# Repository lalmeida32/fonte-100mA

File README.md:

# Projeto: Fonte-100mA — TRABALHO 01

### Grupo 19, Integrantes:

* Adrio O. Alves (*11796830*)
* Eduardo V. B. Rossi (*10716887*)
* Felipi Y. Santos (*11917292*)
* Lucas F. de Almeida (*1162063*)

**Docente**: Eduardo do Valle Simões
**Curso**: SSC0180 - Eletrônica para Computação

**Bacharelado em Ciências da Computação — 2020**
**Instituto de Ciências Matemáticas e de Computação**
**Universidade de São Paulo**

---

# Introdução

​	O projeto de trabalho 1 tem como objetivo a construção de uma fonte de alimentação genérica que precisa  fornecer corrente de até 100mA (*miliampères*) e uma tensão entre 3V e 12V. O projeto conta com um diagrama contendo os componentes eletrônicos escolhidos para construção da fonte, juntamente com o preço de cada um. Além disso, o projeto da fonte foi modelado em duas ferramentas de construção de circuitos: Falstad e EAGLE, e também um vídeo apresentando uma visão geral.

 # O repositório

* **estudo-do-projeto**

  * *Estudos.md*: Esse markdown dá informações do que cada componente eletrônico usado na fonte é, como ele é usado na fonte, isto é, seu papel.

  * **imagens**: fotos de peças/dependência do Estudos.md

  * *Dimensionamento.md*: relação de gastos e links para cada componente

* **arquivos-circuitos**

  * **FONTE**: arquivos do projeto no Eagle (contém esquemático e PCB)
  * *circuit-20200628-2337.circuitjs.txt*: um export do circuito feito no Falstad.
  * **EAGLE:** diretório contendo os arquivos do projeto no EAGLE
  * *eagle.jpg*: um export do projeto esquemático no EAGLE
  * *pcb.png*: um export do projeto em PCB no EAGLE
  * *circuito.png*: foto do circuito no falstad

# Diagrama da Fonte

# Relação componente/valores

**Obs**.: Desconsideramos o frete pois os preços de entrega encontram-se mais elevados durante o período da Pandemia (COVID-19). 

| Componente                                         | Links                                                        | Quantidade | Preço resultante           |
| -------------------------------------------------- | ------------------------------------------------------------ | ---------- | -------------------------- |
| **Transformador**               10+10 bivolt 800mA | https://produto.mercadolivre.com.br/MLB-1304934993-transformador-trafo-1010v-800ma-bivolt-eletrnica-_JM?matt_tool=82322591&matt_word&gclid=CjwKCAjwxLH3BRApEiwAqX9are-Hoqy3DhheSooU8NO5g_m_VOuyIxmSU64KT07Ga4GBR1CclxpqFRoCT10QAvD_BwE&quantity=1 | x1         | R$ 30,00                   |
| **Diodos da ponte retificadora** (1n4007)          | https://www.robocore.net/loja/itens-eletronicos/diodo-1n4007?gclid=CjwKCAjwxLH3BRApEiwAqX9arQYP_1w9nsWFqdvp4X-WlUcxEd8-nIBf6EI5o0YcvvptZfaJRTloMRoCyW0QAvD_BwE | x4         | R$ 0,18        x 4 =  0,72 |
| **Capacitor** eletrolítico 270uF / 50V             | https://produto.mercadolivre.com.br/MLB-1539705638-cap-eletrolitico-270uf-50v-kit-c-50-pcs-_JM?matt_tool=79246729&matt_word&gclid=Cj0KCQjw3Nv3BRC8ARIsAPh8hgJOoLrQkDYLJqg39wcG0bboEYxBCcrLzJXZ2tlZwHFAX_THqohX_jQaArT6EALw_wcB&quantity=1 | x1         | R$ 15,50                   |
| **Diodo Zener** (BZX55C 13V/0,5W)                  | https://www.baudaeletronica.com.br/diodo-zener-bzx55c-13v-0-5w.html | x1         | R$ 0,09                    |
| **Transistor NPN** (BC337)                         | https://www.robocore.net/loja/itens-eletronicos/transistor-npn-bc337?gclid=CjwKCAjwxLH3BRApEiwAqX9arW03jdNyoyxCW0BkSUH1jNxcEZlj1NO8uKe5adsfmaa_ggKm3B1-3hoC9gwQAvD_BwE | x1         | R$ 1,20                    |
| **Resistor** (1kΩ)                                 | https://www.robocore.net/loja/itens-eletronicos/resistor-1k-pacote-com-10-unidades?gclid=Cj0KCQjw3Nv3BRC8ARIsAPh8hgIWM1y2G34SD7-tczS923PPDzohgqbYDrJMymhz6VmJgYpguPpxyvwaAvVsEALw_wcB | x1         | R$ 0,75                    |
| **Resistor** (2.2kΩ)                               | https://www.eletroinfocia.com.br/resistor-1-4w-2k2?parceiro=5383&gclid=Cj0KCQjw3Nv3BRC8ARIsAPh8hgIYW0y8DoWLAFSC3mD8_5y1W9r2wVgBxpERvJd_8GI4131PIfijfdAaArM8EALw_wcB | x1         | R$ 0,10                    |
| **Potenciômetro**                                  | https://www.engetronic-sc.com.br/produtos/ver/321/potenciometro-linear-5k-l15---eixo-estriado-tracking-google-shopping?gclid=Cj0KCQjw3Nv3BRC8ARIsAPh8hgJ0FChjyK9vocYBgfldQy7j2Pse0-l_idTZ0iNpJngsEBgyiqvtofkaAqLBEALw_wcB | x1         | R$ 1,35                    |
| **TOTAL:**                                         |                                                              | 11         | R$ 49,72                   |

# Sobre os componentes não encontrados no EAGLE

​	Como o EAGLE não possui todos os componentes que foram utilizados na fonte, tivemos de utilizar componentes com funcionalidade e dimensões iguais no lugar.

# Links

* Vídeo explicativo da fonte: https://youtu.be/iQQ3Y2TPxfM
* Falstad (cópia em arquivos-circuitos): https://tinyurl.com/y8z7htxh
* Eagle (esquemático): https://imgur.com/a/H5OCaSa
* Eagle (PCB): https://imgur.com/a/zWWUykP

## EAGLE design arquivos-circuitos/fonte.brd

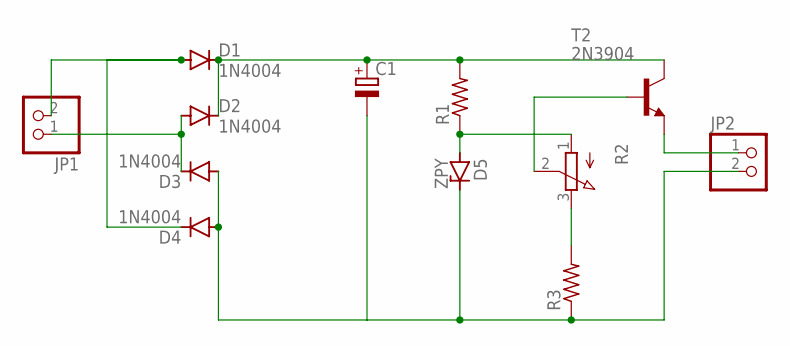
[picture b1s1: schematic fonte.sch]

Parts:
C1: CPOL-EUE3.5-10; E3,5-10
D1, D2, D3, D4: 1N4004; DO41-10
D5: ZPY; DO41Z10
JP1, JP2: PINHD-1X2; 1X02
R1, R3: R-US_0207/10; 0207/10
R2: 3RP/1610N
T2: 2N3904; TO92

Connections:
unnamed: D1.A, D4.C, JP1.2
unnamed: D2.A, D3.C, JP1.1
unnamed: JP2.1, T2.3 (E)
unnamed: C1.+, D1.C, D2.C, R1.2, T2.1 (C)
unnamed: D5.A, R1.1, R2.1 (A)
unnamed: R2.2 (S), T2.2 (B)
unnamed: R2.3 (E), R3.2
unnamed: C1.-, D3.A, D4.A, D5.C, JP2.2, R3.1

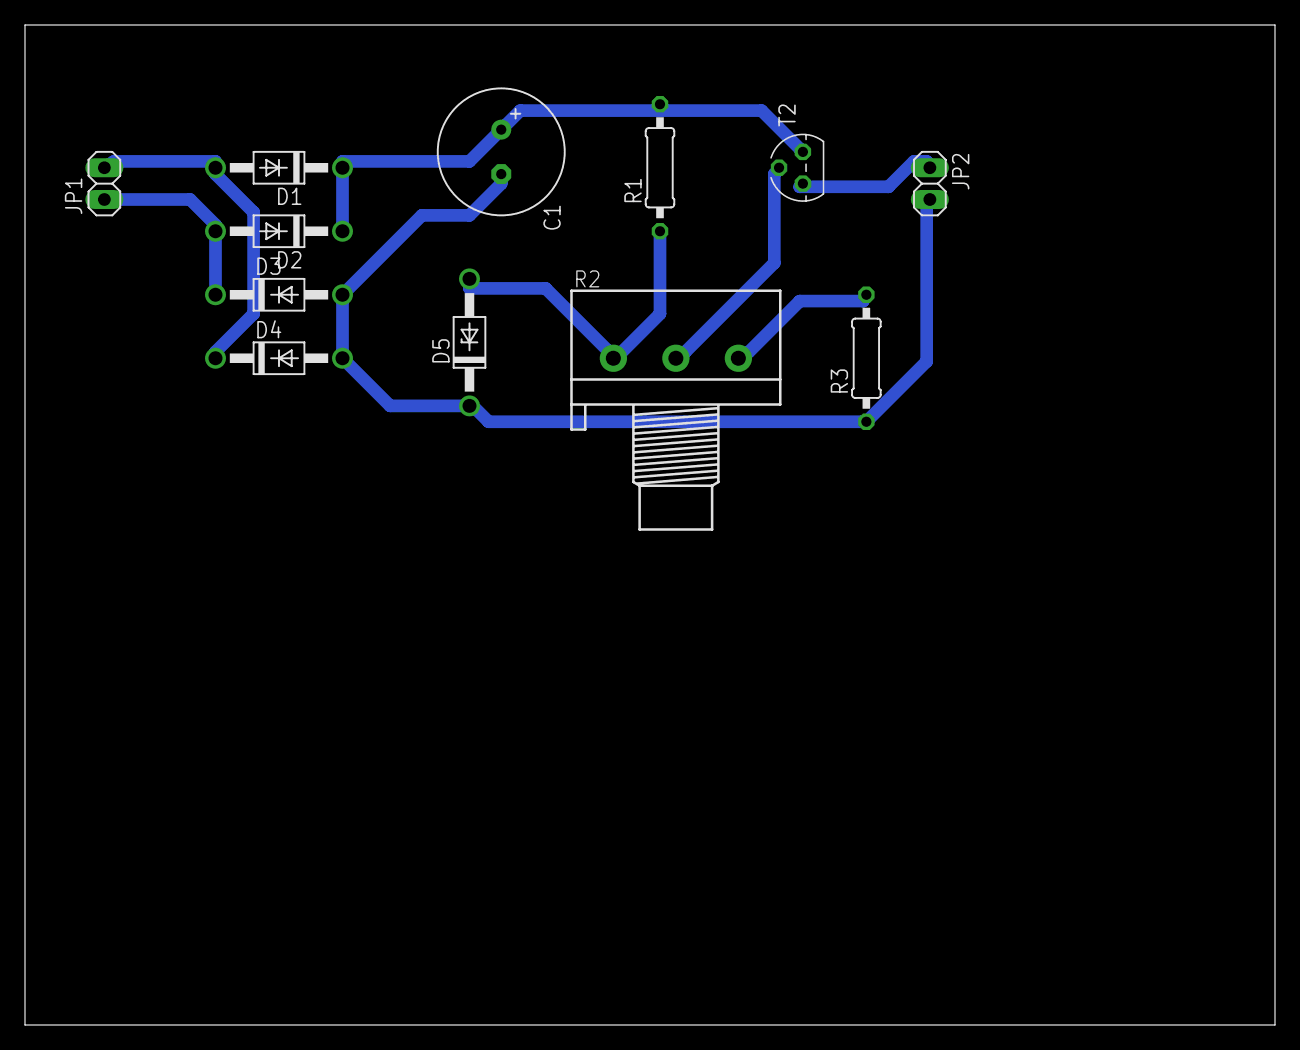
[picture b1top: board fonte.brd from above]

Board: 2 copper layers, 100.0 x 80.0 mm, 12 parts (0 on the bottom side), 8 nets.

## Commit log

2020-05-26 Estudo do Projeto criado
    Adicionados tópicos resistores e capacitores
2020-06-06 Adicionado o Diodo
    Adicionei o diodo no documento do estudo do projeto
2020-06-15 Teste de markdown e imagens adicionadas
2020-06-15 Alteração no caminho da imagem
2020-06-15 Alteração no nome da imagem
2020-06-15 Resistores em linguagem markdown
2020-06-15 Correção de erros
2020-06-15 Capacitor adicionado
2020-06-15 Diodo adicionado
2020-06-15 Diodo completo
2020-06-15 Correção ortográfica diodos
2020-06-15 Diodo zener adicionado
2020-06-15 Correção de erros de ortografia
2020-06-15 Add Transformadores
    Adicionei o tópico do transformadores
2020-06-15 Corrigindo detalhes
2020-06-17 Transformador adicionado
2020-06-17 Potenciômetro adicionado
2020-06-17 Ponte retificadora e correção de erros de gramática
2020-06-17 Adicionado parte do papel do diodo zener
2020-06-18 Alterando o local do transistor e corrigindo as imagens
2020-06-23 Adicionado dimensionamento dos componentes
2020-06-23 dimensionamento reformatado
2020-06-28 Adicionado papel do regulador
2020-06-28 Revisão dos componentes
2020-06-28 Revisão seções da fonte
2020-06-28 Substituindo ponto por vírgula
2020-06-28 Alterando o dimensionamento
2020-06-28 Correção transformador
2020-06-28 Revisão do dimensionamento
2020-06-28 Correção na identação
2020-06-29 Corrigindo um pulo de linha
    Corrigindo um pulo de linha no paragrafo do transformador
2020-06-29 README feito e organização do repositório alterada
2020-06-29 Mudanças nos arquivos
2020-06-29 Correção da imagem no readme
2020-06-29 Revisão no README
2020-06-29 adicionando nova imagem pro circuito
2020-06-29 adicionando no readme a foto do circuito na seção repositório
2020-06-29 README att
2020-06-29 Projeto Eagle
2020-06-29 add projeto eagle
2020-06-29 deletando arquivos sobressalentes
2020-06-29 adicionando descricao do eagle
2020-06-29 add descricao do eagle
2020-06-29 Corrigindo link do readme
2020-06-29 corrigindo link do falstad no readme
